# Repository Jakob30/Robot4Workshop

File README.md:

# Roboterarm – Aufbau und Inbetriebnahme

Dieses Projekt beschreibt den Aufbau und die Inbetriebnahme eines Roboterarms, der mithilfe von 3D-gedruckten Teilen, einer selbstgefertigten Platine und einem STM32F4-Mikrocontroller gesteuert wird.  

---

## 📦 Vorbereitung

1. **3D-Druckteile**  
   - Alle benötigten Teile laut STL-Dateien ausdrucken. Detaillierte Anweisungen befinden sich in dieser [README im Roboterarm Ordner](./Roboterarm/README.md).
   - Qualität und Stabilität der Teile prüfen.  

2. **Bestellung von Bauteilen**  
   - Alle mechanischen und elektronischen Komponenten von der Bestellliste besorgen.  

---

## 🔧 Zusammenbau

Wenn alle 3D-Druckteile und Bauteile vorhanden sind, den Arm gemäß der [**Montageanleitung**](./Roboterarm/Montagehinweise.pdf) zusammenbauen.   

---

## 🖥️ Platine (PCB)

1. **Fertigung**  
   - Platinendaten herunterladen und bei einem Hersteller fertigen lassen. Hinweise zur Platinenfertigung findet man im [Elektronik Ordner](./Elektronik/README.md).

2. **Bestückung**  
   - Bauteile wie Headerpins und Widerstände auf die Platine löten (siehe [README im Elektronik Ordner](./Elektronik/README.md)).  
   - Anschließend können Treiber, Nucleoboard und OLED aufgesteckt werden.

3. **Stromversorgung**  
   - Ein zusätzliches Kabel löten, das den Akku mit der Sicherung, dem Schalter und anschließend mit dem DC/DC-Wandler verbindet.  

---

## ⚙️ STM32F4 – Software

1. **Setup**  
   - [STM32CubeIDE](https://www.st.com/en/development-tools/stm32cubeide.html) installieren.  
   - Projektdateien aus [STM32F4 Ordner](./STM32F4/) importieren.
  
2. **Stromversorgung**  
   - Platine mit Akku oder Netzgerät mit Versorgungsspannung von ca. 15V verbinden.  
   - Schalter umlegen. 
  
3. **Anpassung** 
   - Bewegungen werden im `main.c` programmiert und alle aufzurufenden Funktionen sind in [README](./STM32F4/README.md) beschrieben.  
   - Code per USB auf den Mikrocontroller hochladen.  

---

## 🔍 Kalibrierung mit StallGuard

Vor der ersten Inbetriebnahme ist eine Kalibrierung der StallGuard-Werte notwendig.  
Empfohlen wird die Nutzung von **STM32CubeMonitor**, um Variablen in Echtzeit auszulesen.  

Wichtige Parameter:  
- `STALL_BUFFER_M_X`  
- `LOW_COUNTER_THRESHOLD_M_X`  
- `STALL_MAX_M_X`  

---

## ▶️ Start

1. Vor dem Start den **schwarzen Reset-Knopf** am Nucleo-Board drücken.  
2. Mit dem **blauen Userbutton** das Programm starten.  

---

## 🎥 Beispielvideo

Einen Eindruck, wie der fertige Roboterarm aussehen kann, gibt es hier:  
[➡️ Video ansehen](https://www.dropbox.com/scl/fi/g09jmz12r2tmc5cvw9wto/Robot4Workshop_v4.mp4?rlkey=lwdefdrdfxj2pr9vu0g0xlj73&st=269ooo00&dl=0)

---

## ✅ Hinweis

- Alle Arbeitsschritte sorgfältig durchführen.  
- Sicherheitsaspekte beim Umgang mit Stromversorgung und Lötarbeiten beachten.

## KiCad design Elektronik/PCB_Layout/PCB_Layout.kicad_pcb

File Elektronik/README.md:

# Elektronik – PCB_Layout (KiCad)

Diese README beschreibt **alles rund um die Leiterplatte**: warum KiCad, was im Ordner `PCB_Layout/` liegt, wie du die Platine **fertigen lässt**, **Bauteile bestellst**, **bestückst** und **in Betrieb nimmst**.

---

## Warum KiCad?

* **Open‑Source & kostenlos**: Reproduzierbar für alle – ideal für ein Open‑Hardware‑Projekt.
* **Versionierbar**: Textbasierte Projektdateien → gut in Git nutzbar.
* **Ökosystem**: iBOM, DRC/ERC‑Checks, Plugin‑Support.

> Getestet mit **KiCad 8.x**. Ältere Versionen funktionieren u. U. nicht.

---

## Ordnerstruktur

```
Elektronik/
└─ PCB_Layout/
   ├─ PCB_Layout.kicad_pro           # Projektdatei (KiCad 8)
   ├─ PCB_Layout.kicad_sch           # Top‑Schaltplan (inkl. Hierarchie)
   ├─ PCB_Layout.kicad_pcb           # Leiterplattenlayout
   ├─ power.kicad_sch                # Sheet: Versorgung/15 V → 5 V 
   ├─ nucleo_F446RE.kicad_sch        # Sheet: NUCLEO‑F446RE 
   ├─ motor_driver.kicad_sch         # Sheet: TMC2209‑Treiber & Motoranschlüsse
   ├─ display_und_LED.kicad_sch      # Sheet: OLED, LEDs
   ├─ AOM12864A0-1.54WW-ANO/         # **Custom Footprint/Symbol** (OLED 1.54")
   ├─ DM-OLED096-636/                # **Custom Footprint/Symbol** (OLED 0.96")
   ├─ NUCLEO-F446RE/                 # **Custom Footprint/Symbol** (Nucleo STM32)
   ├─ TMC2209_SILENTSTEPSTICK/       # **Custom Footprint/Symbol** (Treiber‑Modul)
   ├─ PCB_Layout----
```

**Hinweis zu den Unterordnern:** `AOM12864…`, `DM‑OLED096‑636`, `NUCLEO‑F446RE`, `TMC2209_SILENTSTEPSTICK` enthalten die **projektspezifischen Bibliotheken** (Symbole/Footprints), die **nicht in KiCads Standard‑Libs** vorhanden sind. Damit bleibt das Projekt **voll reproduzierbar**.

---

## Platinenfertigung – Schritt für Schritt

### 1) Gerber/Bohrdaten erzeugen (KiCad)

1. Projekt öffnen → PCB-Editor.
2. **Datei → Plot**

   * Format: **Gerber**
   * Lagen (typisch 2‑lagig): `F.Cu`, `B.Cu`, `F.SilkS`, `B.SilkS`, `F.Mask`, `B.Mask`, `Edge.Cuts` (ggf. `F.Paste/B.Paste` bei Reflow‑SMD)
   * Allgemeine Optionen → Abwählen **Footprintwerte plotten**
   * **Plotten** → anschl. **Bohrdateien generieren**.

3. **ZIP‑Archiv** aus allen Gerber + Drill → `fabrication/<projekt>_gerbers.zip`.

### 2) Hersteller auswählen & bestellen

Wir haben u. a. bei **Multi‑CB** (Multi Circuit Boards) gefertigt: [https://portal.multi-circuit-boards.eu/](https://portal.multi-circuit-boards.eu/)

**Vorgehen (Beispiel Multi‑CB):**

1. Portal öffnen → Online‑Kalkulator → **Optional: CAD-Datei automatisch auslesen** klicken → **Datei anhängen** und dann `fabrication/<projekt>_gerbers.zip` hochladen.
2. Stückzahl auswählen (z. B. 5–10 Stück) & Lieferzeit.
4. Bestellung abschließen.

> Andere Fertiger funktionieren ebenso, solange sie Standard‑Gerber akzeptieren.

---

## Stückliste (BOM) & Bauteilbestellung

### 1) BOM in KiCad erzeugen

* **Schaltplan‑Editor → Werkzeuge → Stückliste (BoM) erstellen** 
* **Exportieren** als CSV → `outputs/bom.csv`.

### 2) Teile kaufen

* Öffne `bom.csv` → bestelle nach **MPN** (Manufacturer Part Number) bei Distributor deiner Wahl (z. B. Conrad, Mouser, etc.).
* Die restlichen Module (z. B. **TMC2209 Treiber**, **NUCLEO‑F446RE**, **OLED 0.96"**) findest du in [dieser Bestellliste](../Bestellliste.xlsx)

> Tipp: SMD Widerstände/Kondensatoren sind i. d. R. 1206 Hand‑Solder‑freundlich.

---

## Bestückung & Montage

### Reihenfolge (empfohlen)

1. **SMD zuerst**, klein → groß (falls SMD vorhanden). Reflow oder Handlötung.
2. **THT** (Stiftleisten, Buchsenleisten, Schraubklemmen).

>Hinweis: Unten auf dem PCB sieht man, dass die Treiber, MCU und OLED Display direkt auf dem PCB gelötet werden können. Allerdings empfehlen wir, die Buchsenleisten an diesen Stellen zu löten und dann Treiber, MCU, Display darauf zu stecken. Damit lassen sich diese Bauteile problemlos ein-/ausstecken, ohne entlöten zu müssen. 

3. **Module** stecken:

   * **TMC2209**‑Module in korrekter **Orientierung** (Silkscreen‑Pfeile/Pin‑1). **Falsches Stecken zerstört den Treiber!**
   * **NUCLEO‑F446RE** Board/Socket einsetzen.
   * **OLED/LEDs** nach Polung.

> **Nie** Module stecken/ziehen, solange die Platine unter Spannung steht.

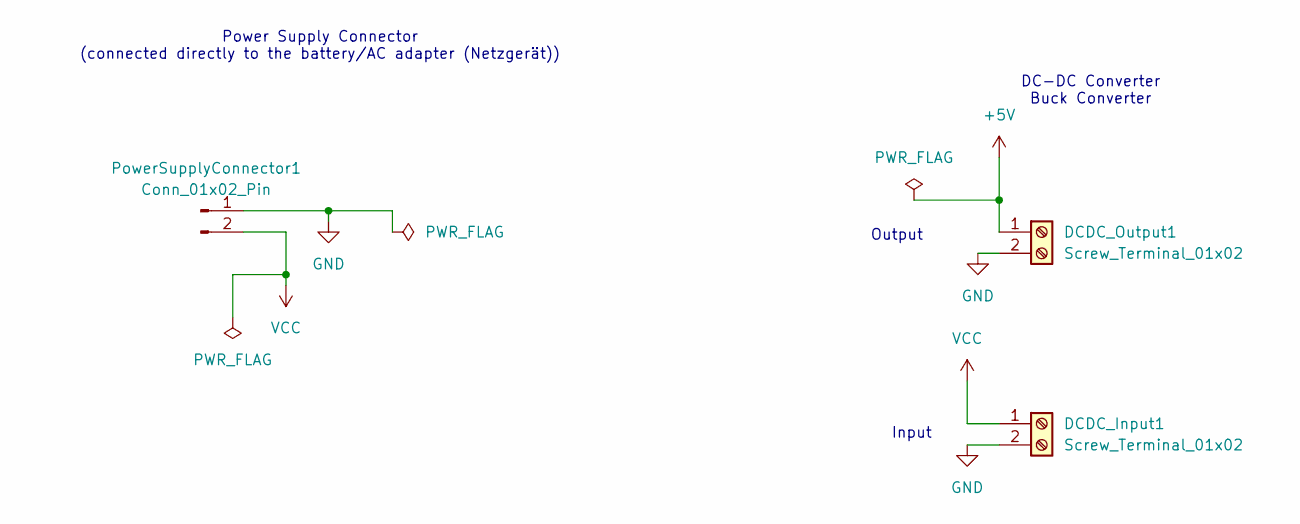
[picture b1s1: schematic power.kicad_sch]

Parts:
DCDC_Input1: Screw_Terminal_01x02; TerminalBlock_Phoenix_PT-1,5-2-5.0-H_1x02_P5.00mm_Horizontal
DCDC_Output1: Screw_Terminal_01x02; DC_DC_Converter_with_Screw_Terminal
PowerSupplyConnector1: Conn_01x02_Pin; AMASS_XT60-M_1x02_P7.20mm_Vertical

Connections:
+5V: DCDC_Output1.1; also elsewhere on the board
GND: DCDC_Input1.2, DCDC_Output1.2, PowerSupplyConnector1.1; also elsewhere on the board
VCC: DCDC_Input1.1, PowerSupplyConnector1.2; also elsewhere on the board

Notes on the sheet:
Input
Power Supply Connector (connected directly to the battery/AC adapter (Netzgerät))
Output
DC-DC Converter Buck Converter

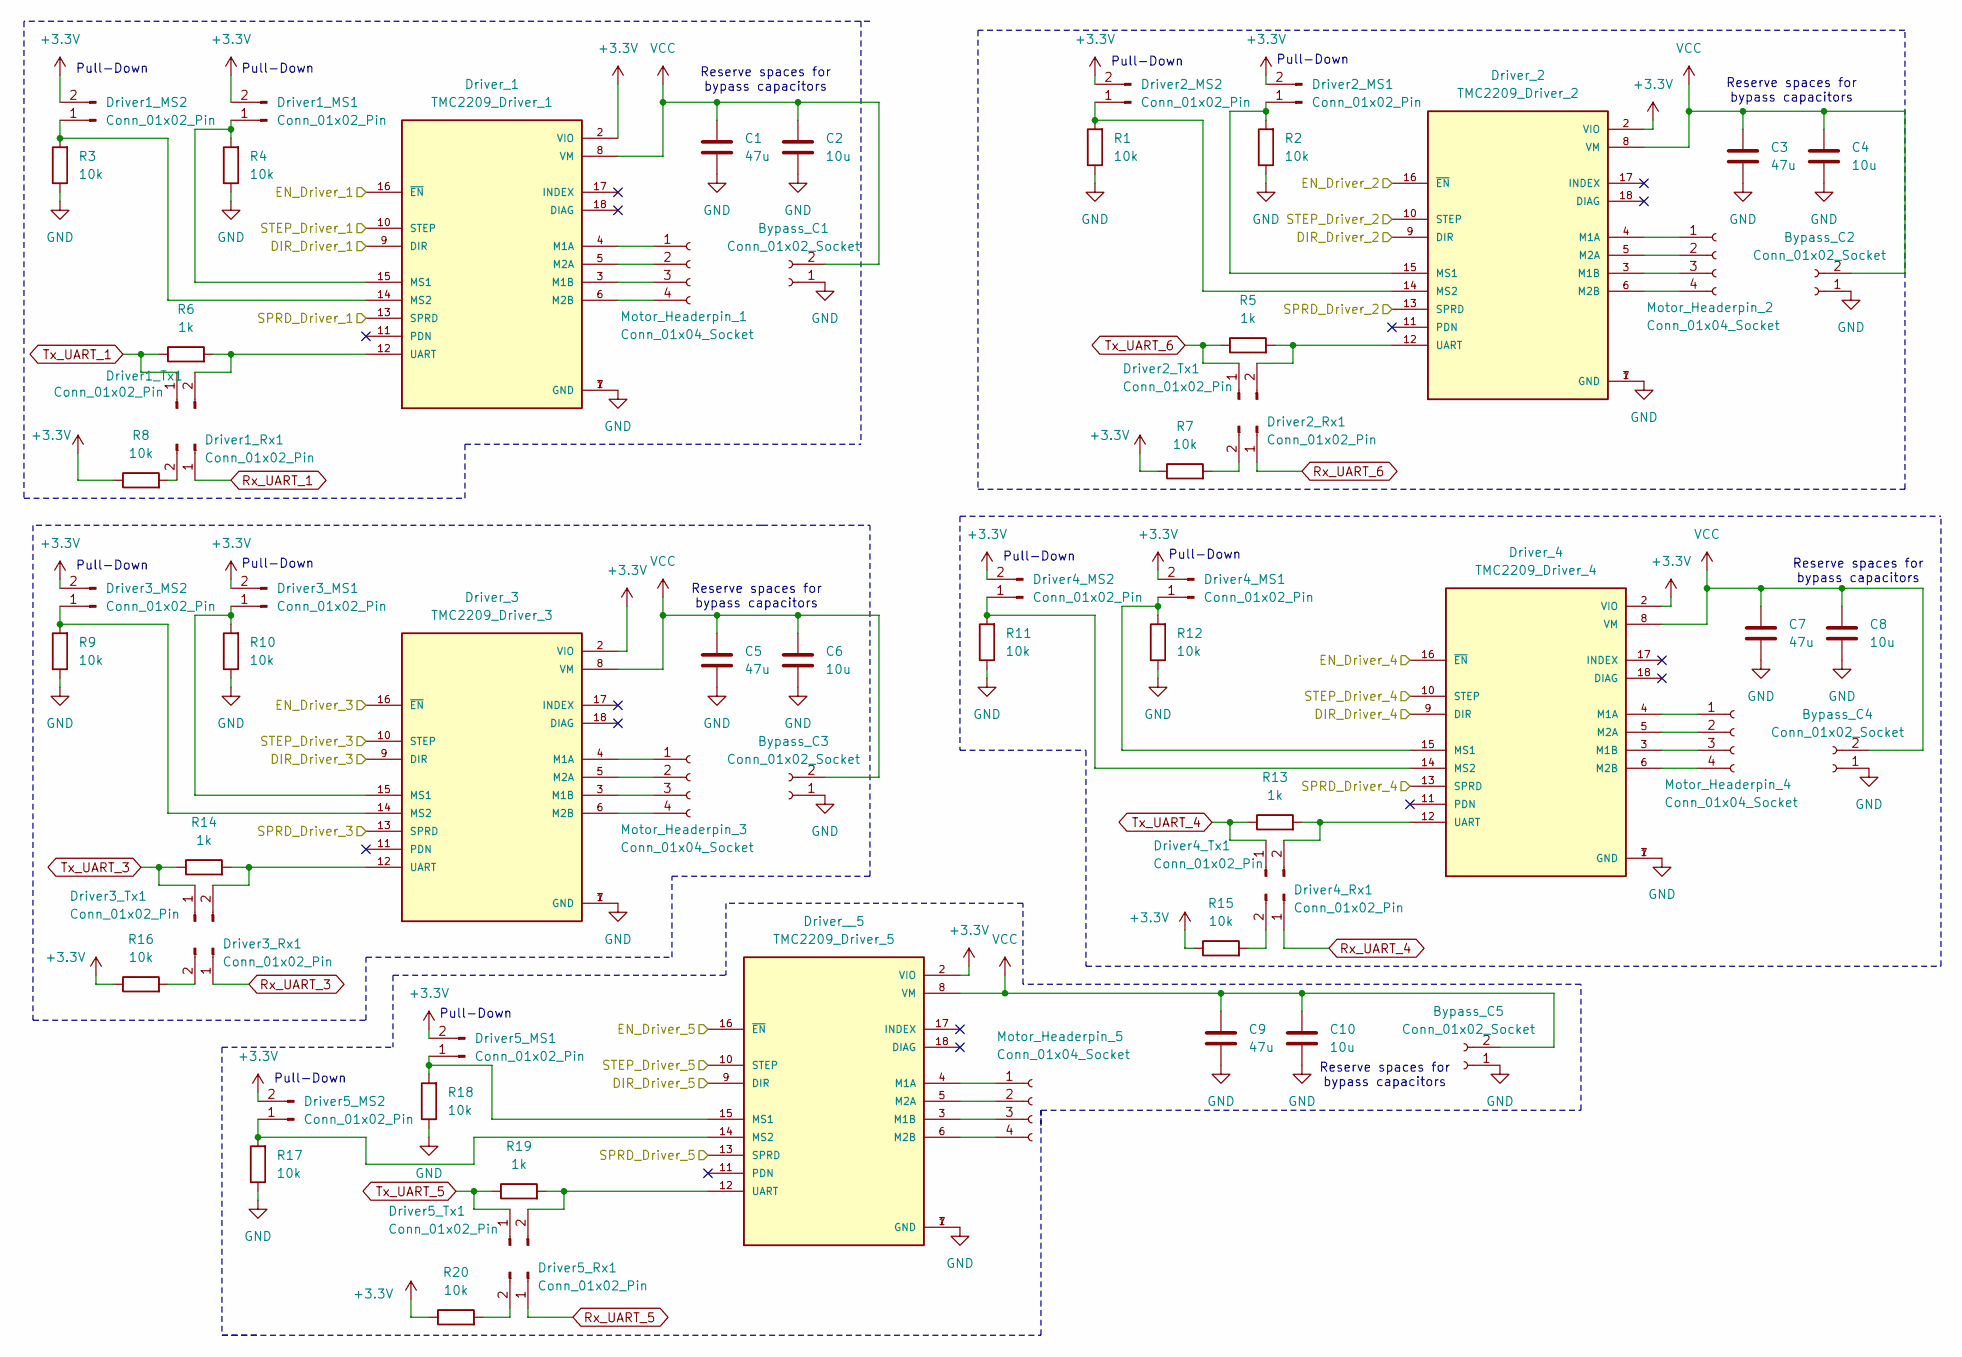
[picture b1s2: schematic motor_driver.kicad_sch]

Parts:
Bypass_C1, Bypass_C2, Bypass_C3, Bypass_C4, Bypass_C5: Conn_01x02_Socket; PinSocket_1x02_P2.54mm_Vertical_SMD_Pin1Left
C1, C3, C5, C7, C9: 47u; C_1206_3216Metric_Pad1.33x1.80mm_HandSolder
C2, C4, C6, C8, C10: 10u; C_1206_3216Metric_Pad1.33x1.80mm_HandSolder
Driver1_MS1, Driver1_MS2, Driver1_Rx1, Driver1_Tx1, Driver2_MS1, Driver2_MS2, Driver2_Rx1, Driver2_Tx1, Driver3_MS1, Driver3_MS2, Driver3_Rx1, Driver3_Tx1, Driver4_MS1, Driver4_MS2, Driver4_Rx1, Driver4_Tx1, Driver5_MS1, Driver5_MS2, Driver5_Rx1, Driver5_Tx1: Conn_01x02_Pin; PinHeader_1x02_P2.54mm_Vertical_SMD_Pin1Left
Driver_1: TMC2209_Driver_1; MODULE_TMC2209_SILENTSTEPSTICK; PARTREV 1.20
Driver_2: TMC2209_Driver_2; MODULE_TMC2209_SILENTSTEPSTICK; PARTREV 1.20
Driver_3: TMC2209_Driver_3; MODULE_TMC2209_SILENTSTEPSTICK; PARTREV 1.20
Driver_4: TMC2209_Driver_4; MODULE_TMC2209_SILENTSTEPSTICK; PARTREV 1.20
Driver__5: TMC2209_Driver_5; MODULE_TMC2209_SILENTSTEPSTICK; PARTREV 1.20
Motor_Headerpin_1, Motor_Headerpin_2, Motor_Headerpin_3, Motor_Headerpin_4, Motor_Headerpin_5: Conn_01x04_Socket; PinSocket_1x04_P2.54mm_Vertical
R1, R2, R3, R4, R7, R8, R9, R10, R11, R12, R15, R16, R17, R18, R20: 10k; R_1206_3216Metric_Pad1.30x1.75mm_HandSolder
R5, R6, R13, R14, R19: 1k; R_1206_3216Metric_Pad1.30x1.75mm_HandSolder

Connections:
+3.3V: Driver1_MS1.2, Driver1_MS2.2, Driver2_MS1.2, Driver2_MS2.2, Driver3_MS1.2, Driver3_MS2.2, Driver4_MS1.2, Driver4_MS2.2, Driver5_MS1.2, Driver5_MS2.2, Driver_1.2 (VIO), Driver_2.2 (VIO), Driver_3.2 (VIO), Driver_4.2 (VIO), Driver__5.2 (VIO), R7.1, R8.1, R15.1, R16.1, R20.1; also elsewhere on the board
/motor_driver/DIR_Driver_1: Driver_1.9 (DIR); also elsewhere on the board
/motor_driver/DIR_Driver_2: Driver_2.9 (DIR); also elsewhere on the board
/motor_driver/DIR_Driver_3: Driver_3.9 (DIR); also elsewhere on the board
/motor_driver/DIR_Driver_4: Driver_4.9 (DIR); also elsewhere on the board
/motor_driver/DIR_Driver_5: Driver__5.9 (DIR); also elsewhere on the board
/motor_driver/EN_Driver_1: Driver_1.16 (~EN); also elsewhere on the board
/motor_driver/EN_Driver_2: Driver_2.16 (~EN); also elsewhere on the board
/motor_driver/EN_Driver_3: Driver_3.16 (~EN); also elsewhere on the board
/motor_driver/EN_Driver_4: Driver_4.16 (~EN); also elsewhere on the board
/motor_driver/EN_Driver_5: Driver__5.16 (~EN); also elsewhere on the board
/motor_driver/SPRD_Driver_1: Driver_1.13 (SPRD); also elsewhere on the board
/motor_driver/SPRD_Driver_2: Driver_2.13 (SPRD); also elsewhere on the board
/motor_driver/SPRD_Driver_3: Driver_3.13 (SPRD); also elsewhere on the board
/motor_driver/SPRD_Driver_4: Driver_4.13 (SPRD); also elsewhere on the board
/motor_driver/SPRD_Driver_5: Driver__5.13 (SPRD); also elsewhere on the board
/motor_driver/STEP_Driver_1: Driver_1.10 (STEP); also elsewhere on the board
/motor_driver/STEP_Driver_2: Driver_2.10 (STEP); also elsewhere on the board
/motor_driver/STEP_Driver_3: Driver_3.10 (STEP); also elsewhere on the board
/motor_driver/STEP_Driver_4: Driver_4.10 (STEP); also elsewhere on the board
/motor_driver/STEP_Driver_5: Driver__5.10 (STEP); also elsewhere on the board
GND: Bypass_C1.1, Bypass_C2.1, Bypass_C3.1, Bypass_C4.1, Bypass_C5.1, C1.2, C2.2, C3.2, C4.2, C5.2, C6.2, C7.2, C8.2, C9.2, C10.2, Driver_1.1 (GND), Driver_1.7 (GND), Driver_2.1 (GND), Driver_2.7 (GND), Driver_3.1 (GND), Driver_3.7 (GND), Driver_4.1 (GND), Driver_4.7 (GND), Driver__5.1 (GND), Driver__5.7 (GND), R1.1, R2.1, R3.1, R4.1, R9.1, R10.1, R11.1, R12.1, R17.1, R18.1; also elsewhere on the board
unnamed: Driver1_MS1.1, Driver_1.15 (MS1), R4.2
unnamed: Driver1_MS2.1, Driver_1.14 (MS2), R3.2
unnamed: Driver1_Rx1.2, R8.2
unnamed: Driver1_Tx1.2, Driver_1.12 (UART), R6.2
unnamed: Driver2_MS1.1, Driver_2.15 (MS1), R2.2
unnamed: Driver2_MS2.1, Driver_2.14 (MS2), R1.2
unnamed: Driver2_Rx1.2, R7.2
unnamed: Driver2_Tx1.2, Driver_2.12 (UART), R5.2
unnamed: Driver3_MS1.1, Driver_3.15 (MS1), R10.2
unnamed: Driver3_MS2.1, Driver_3.14 (MS2), R9.2
unnamed: Driver3_Rx1.2, R16.2
unnamed: Driver3_Tx1.2, Driver_3.12 (UART), R14.2
unnamed: Driver4_MS1.1, Driver_4.15 (MS1), R12.2
unnamed: Driver4_MS2.1, Driver_4.14 (MS2), R11.2
unnamed: Driver4_Rx1.2, R15.2
unnamed: Driver4_Tx1.2, Driver_4.12 (UART), R13.2
unnamed: Driver5_MS1.1, Driver__5.15 (MS1), R18.2
unnamed: Driver5_MS2.1, Driver__5.14 (MS2), R17.2
unnamed: Driver5_Rx1.2, R20.2
unnamed: Driver5_Tx1.2, Driver__5.12 (UART), R19.2
unnamed: Driver_1.4 (M1A), Motor_Headerpin_1.1
unnamed: Driver_1.3 (M1B), Motor_Headerpin_1.3
unnamed: Driver_1.5 (M2A), Motor_Headerpin_1.2
unnamed: Driver_1.6 (M2B), Motor_Headerpin_1.4
unnamed: Driver_2.4 (M1A), Motor_Headerpin_2.1
unnamed: Driver_2.3 (M1B), Motor_Headerpin_2.3
unnamed: Driver_2.5 (M2A), Motor_Headerpin_2.2
unnamed: Driver_2.6 (M2B), Motor_Headerpin_2.4
unnamed: Driver_3.4 (M1A), Motor_Headerpin_3.1
unnamed: Driver_3.3 (M1B), Motor_Headerpin_3.3
unnamed: Driver_3.5 (M2A), Motor_Headerpin_3.2
unnamed: Driver_3.6 (M2B), Motor_Headerpin_3.4
unnamed: Driver_4.4 (M1A), Motor_Headerpin_4.1
unnamed: Driver_4.3 (M1B), Motor_Headerpin_4.3
unnamed: Driver_4.5 (M2A), Motor_Headerpin_4.2
unnamed: Driver_4.6 (M2B), Motor_Headerpin_4.4
unnamed: Driver__5.4 (M1A), Motor_Headerpin_5.1
unnamed: Driver__5.3 (M1B), Motor_Headerpin_5.3
unnamed: Driver__5.5 (M2A), Motor_Headerpin_5.2
unnamed: Driver__5.6 (M2B), Motor_Headerpin_5.4
Rx_UART_1: Driver1_Rx1.1; also elsewhere on the board
Rx_UART_3: Driver3_Rx1.1; also elsewhere on the board
Rx_UART_4: Driver4_Rx1.1; also elsewhere on the board
Rx_UART_5: Driver5_Rx1.1; also elsewhere on the board
Rx_UART_6: Driver2_Rx1.1; also elsewhere on the board
Tx_UART_1: Driver1_Tx1.1, R6.1; also elsewhere on the board
Tx_UART_3: Driver3_Tx1.1, R14.1; also elsewhere on the board
Tx_UART_4: Driver4_Tx1.1, R13.1; also elsewhere on the board
Tx_UART_5: Driver5_Tx1.1, R19.1; also elsewhere on the board
Tx_UART_6: Driver2_Tx1.1, R5.1; also elsewhere on the board
VCC: Bypass_C1.2, Bypass_C2.2, Bypass_C3.2, Bypass_C4.2, Bypass_C5.2, C1.1, C2.1, C3.1, C4.1, C5.1, C6.1, C7.1, C8.1, C9.1, C10.1, Driver_1.8 (VM), Driver_2.8 (VM), Driver_3.8 (VM), Driver_4.8 (VM), Driver__5.8 (VM); also elsewhere on the board

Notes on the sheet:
Reserve spaces for bypass capacitors
Pull-Down
Reserve spaces for bypass capacitors

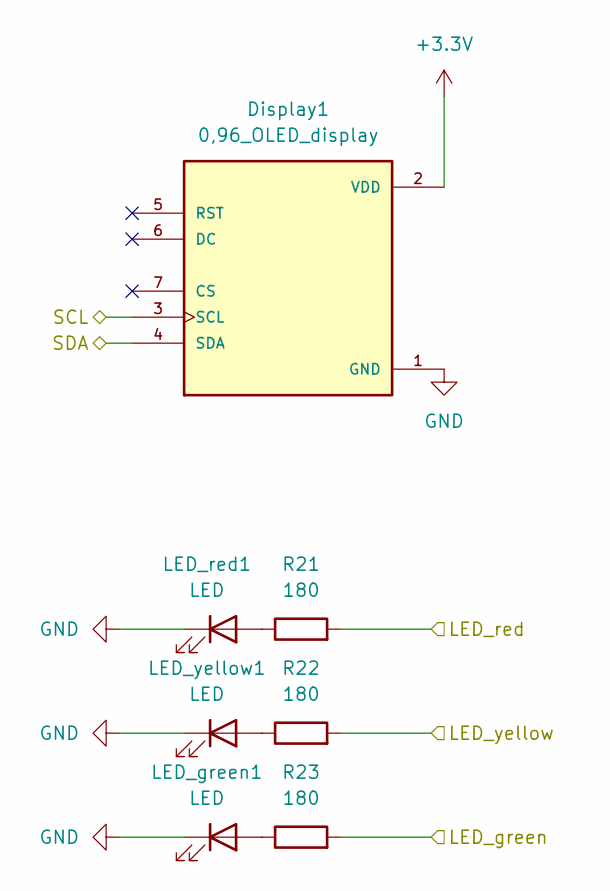
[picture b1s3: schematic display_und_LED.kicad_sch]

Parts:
Display1: 0,96_OLED_display; 0,96_OLED_Display; PARTREV O
LED_green1: LED; LED_D5.0mm
LED_red1: LED; LED_D5.0mm
LED_yellow1: LED; LED_D5.0mm
R21, R22, R23: 180; R_1206_3216Metric_Pad1.30x1.75mm_HandSolder

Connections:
+3.3V: Display1.2 (VDD); also elsewhere on the board
/display_und_LED/LED_green: R23.2; also elsewhere on the board
/display_und_LED/LED_red: R21.2; also elsewhere on the board
/display_und_LED/LED_yellow: R22.2; also elsewhere on the board
/display_und_LED/SCL: Display1.3 (SCL); also elsewhere on the board
/display_und_LED/SDA: Display1.4 (SDA); also elsewhere on the board
GND: Display1.1 (GND), LED_green1.1 (K), LED_red1.1 (K), LED_yellow1.1 (K); also elsewhere on the board
unnamed: LED_green1.2 (A), R23.1
unnamed: LED_red1.2 (A), R21.1
unnamed: LED_yellow1.2 (A), R22.1

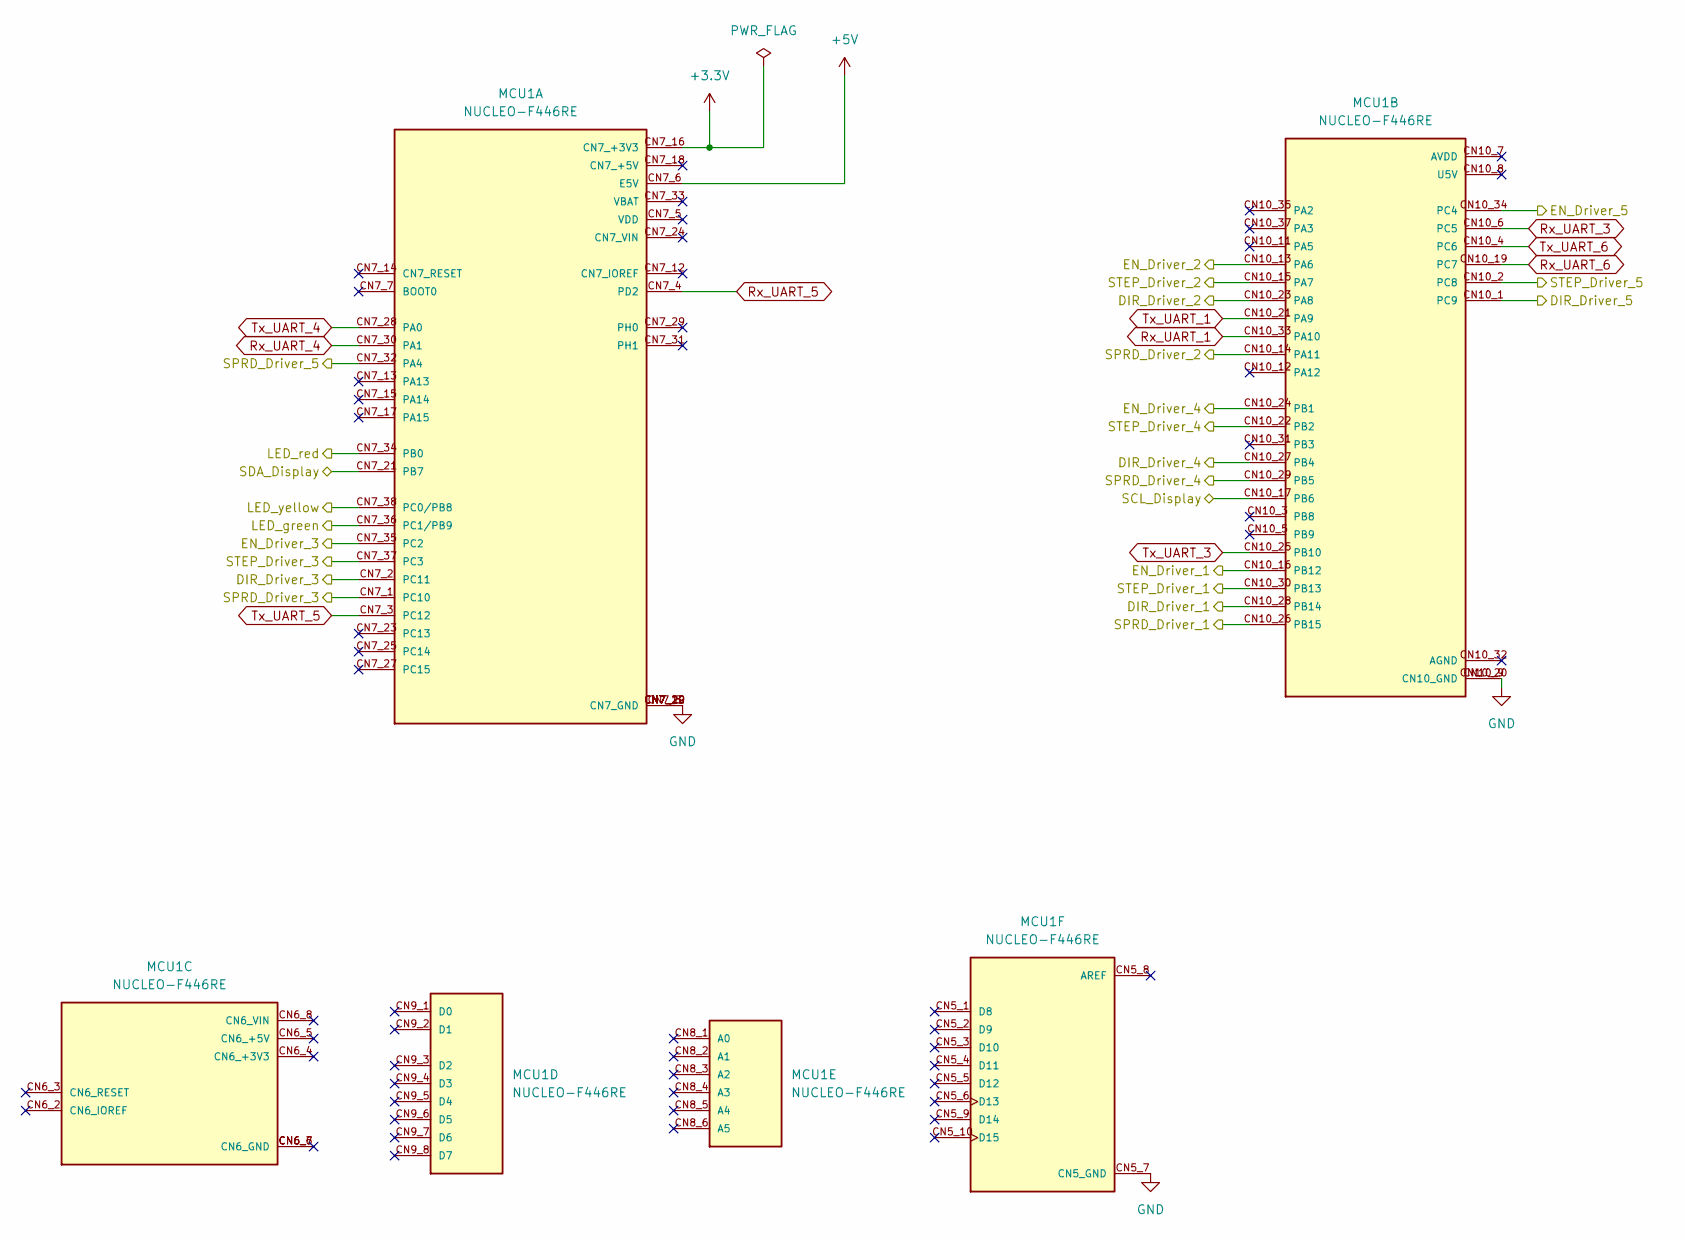
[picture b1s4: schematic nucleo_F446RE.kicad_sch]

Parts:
MCU1: NUCLEO-F446RE; MODULE_NUCLEO-F446RE; PARTREV 13

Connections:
+3.3V: MCU1.CN7_16 (CN7_+3V3); also elsewhere on the board
+5V: MCU1.CN7_6 (E5V); also elsewhere on the board
/display_und_LED/LED_green: MCU1.CN7_36 (PC1/PB9); also elsewhere on the board
/display_und_LED/LED_red: MCU1.CN7_34 (PB0); also elsewhere on the board
/display_und_LED/LED_yellow: MCU1.CN7_38 (PC0/PB8); also elsewhere on the board
/display_und_LED/SCL: MCU1.CN10_17 (PB6); also elsewhere on the board
/display_und_LED/SDA: MCU1.CN7_21 (PB7); also elsewhere on the board
/motor_driver/DIR_Driver_1: MCU1.CN10_28 (PB14); also elsewhere on the board
/motor_driver/DIR_Driver_2: MCU1.CN10_23 (PA8); also elsewhere on the board
/motor_driver/DIR_Driver_3: MCU1.CN7_2 (PC11); also elsewhere on the board
/motor_driver/DIR_Driver_4: MCU1.CN10_27 (PB4); also elsewhere on the board
/motor_driver/DIR_Driver_5: MCU1.CN10_1 (PC9); also elsewhere on the board
/motor_driver/EN_Driver_1: MCU1.CN10_16 (PB12); also elsewhere on the board
/motor_driver/EN_Driver_2: MCU1.CN10_13 (PA6); also elsewhere on the board
/motor_driver/EN_Driver_3: MCU1.CN7_35 (PC2); also elsewhere on the board
/motor_driver/EN_Driver_4: MCU1.CN10_24 (PB1); also elsewhere on the board
/motor_driver/EN_Driver_5: MCU1.CN10_34 (PC4); also elsewhere on the board
/motor_driver/SPRD_Driver_1: MCU1.CN10_26 (PB15); also elsewhere on the board
/motor_driver/SPRD_Driver_2: MCU1.CN10_14 (PA11); also elsewhere on the board
/motor_driver/SPRD_Driver_3: MCU1.CN7_1 (PC10); also elsewhere on the board
/motor_driver/SPRD_Driver_4: MCU1.CN10_29 (PB5); also elsewhere on the board
/motor_driver/SPRD_Driver_5: MCU1.CN7_32 (PA4); also elsewhere on the board
/motor_driver/STEP_Driver_1: MCU1.CN10_30 (PB13); also elsewhere on the board
/motor_driver/STEP_Driver_2: MCU1.CN10_15 (PA7); also elsewhere on the board
/motor_driver/STEP_Driver_3: MCU1.CN7_37 (PC3); also elsewhere on the board
/motor_driver/STEP_Driver_4: MCU1.CN10_22 (PB2); also elsewhere on the board
/motor_driver/STEP_Driver_5: MCU1.CN10_2 (PC8); also elsewhere on the board
GND: MCU1.CN5_7 (CN5_GND), MCU1.CN7_8 (CN7_GND), MCU1.CN7_19 (CN7_GND), MCU1.CN7_20 (CN7_GND), MCU1.CN7_22 (CN7_GND), MCU1.CN10_9 (CN10_GND), MCU1.CN10_20 (CN10_GND); also elsewhere on the board
Rx_UART_1: MCU1.CN10_33 (PA10); also elsewhere on the board
Rx_UART_3: MCU1.CN10_6 (PC5); also elsewhere on the board
Rx_UART_4: MCU1.CN7_30 (PA1); also elsewhere on the board
Rx_UART_5: MCU1.CN7_4 (PD2); also elsewhere on the board
Rx_UART_6: MCU1.CN10_19 (PC7); also elsewhere on the board
Tx_UART_1: MCU1.CN10_21 (PA9); also elsewhere on the board
Tx_UART_3: MCU1.CN10_25 (PB10); also elsewhere on the board
Tx_UART_4: MCU1.CN7_28 (PA0); also elsewhere on the board
Tx_UART_5: MCU1.CN7_3 (PC12); also elsewhere on the board
Tx_UART_6: MCU1.CN10_4 (PC6); also elsewhere on the board

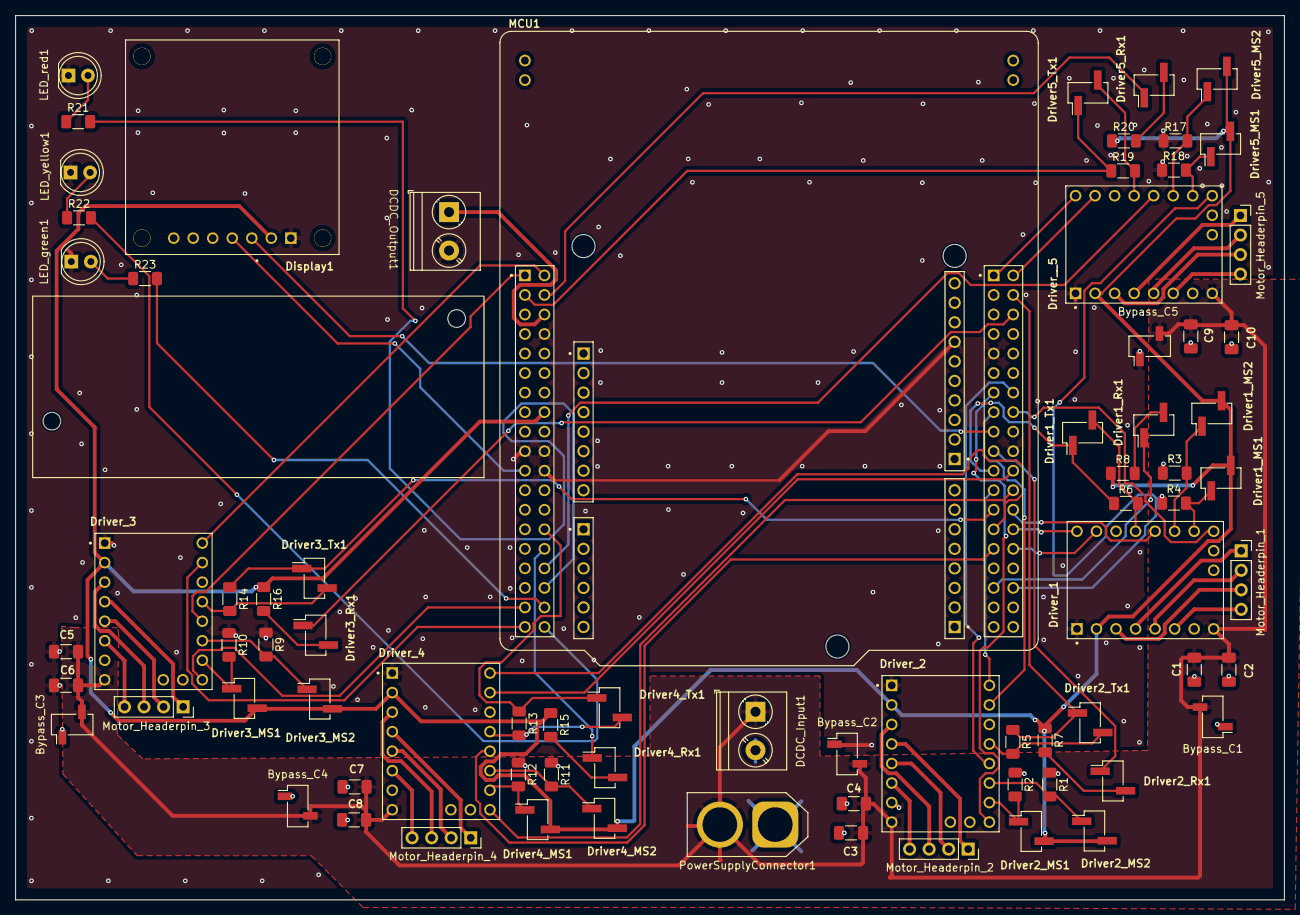
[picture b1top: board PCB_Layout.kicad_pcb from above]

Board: 2 copper layers, 165.0 x 115.0 mm, 76 parts (0 on the bottom side), 82 nets.

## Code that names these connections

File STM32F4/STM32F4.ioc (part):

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Mcu.Name=STM32F446R(C-E)Tx
Mcu.Package=LQFP64
Mcu.UserName=STM32F446RETx
PA0-WKUP.Mode=Asynchronous
PA0-WKUP.Signal=UART4_TX
PA1.Mode=Asynchronous
PA1.Signal=UART4_RX
PA10.Mode=Asynchronous
PA10.Signal=USART1_RX
PA11.Signal=GPIO_Input
PA13.GPIOParameters=GPIO_Label
PA13.GPIO_Label=TMS
PA13.Mode=Serial_Wire
PA13.Signal=SYS_JTMS-SWDIO
PA14.GPIOParameters=GPIO_Label
PA14.GPIO_Label=TCK
PA14.Mode=Serial_Wire
PA14.Signal=SYS_JTCK-SWCLK
PA2.GPIOParameters=GPIO_PuPd,GPIO_Label,GPIO_ModeDefaultOD
PA2.GPIO_Label=USART_TX
PA2.GPIO_ModeDefaultOD=GPIO_MODE_AF_OD
PA2.GPIO_PuPd=GPIO_NOPULL
PA2.Mode=Asynchronous
PA2.Signal=USART2_TX
PA3.GPIOParameters=GPIO_Label
PA3.GPIO_Label=USART_RX
PA3.Mode=Asynchronous
PA3.Signal=USART2_RX
PA4.Signal=GPIO_Input
PA5.GPIOParameters=GPIO_Label
PA5.GPIO_Label=LD2 [Green Led]
PA5.Signal=GPIO_Output
PA6.GPIOParameters=GPIO_Label
PA6.GPIO_Label=MOT_EN_2
PA6.Signal=GPIO_Output
PA7.GPIOParameters=GPIO_Label
PA7.GPIO_Label=STEP_2
PA7.Signal=GPIO_Output
PA8.GPIOParameters=GPIO_Label
PA8.GPIO_Label=DIR_2
PA8.Signal=GPIO_Output
PA9.GPIOParameters=GPIO_PuPd
PA9.GPIO_PuPd=GPIO_NOPULL
PA9.Mode=Asynchronous
PA9.Signal=USART1_TX
PB0.GPIOParameters=GPIO_Label
PB0.GPIO_Label=LED_red
PB0.Signal=GPIO_Output
PB1.GPIOParameters=GPIO_Label
PB1.GPIO_Label=MOT_EN_4
PB1.Signal=GPIO_Output
PB10.Mode=Asynchronous
PB10.Signal=USART3_TX
PB12.GPIOParameters=GPIO_Label
PB12.GPIO_Label=MOT_EN_1
PB12.Signal=GPIO_Output
PB13.GPIOParameters=GPIO_Label
PB13.GPIO_Label=STEP_1
PB13.Signal=GPIO_Output
PB14.GPIOParameters=GPIO_Label
PB14.GPIO_Label=DIR_1
PB14.Signal=GPIO_Output
PB15.Signal=GPIO_Input
PB2.GPIOParameters=GPIO_Label
PB2.GPIO_Label=STEP_4
PB2.Signal=GPIO_Output
PB3.GPIOParameters=GPIO_Label
PB3.GPIO_Label=SWO
PB3.Signal=SYS_JTDO-SWO
PB4.GPIOParameters=GPIO_Label
PB4.GPIO_Label=DIR_4
PB4.Signal=GPIO_Output
PB5.Signal=GPIO_Input
PB6.Mode=I2C
PB6.Signal=I2C1_SCL
PB7.Mode=I2C
PB7.Signal=I2C1_SDA
PB9.GPIOParameters=GPIO_Label
PB9.GPIO_Label=DIAG_3
PB9.Signal=GPIO_Input
PC0.GPIOParameters=GPIO_Label
PC0.GPIO_Label=LED_yellow
PC0.Signal=GPIO_Output
PC1.GPIOParameters=GPIO_Label
PC1.GPIO_Label=LED_green
PC1.Signal=GPIO_Output
PC10.Signal=GPIO_Input
PC11.GPIOParameters=GPIO_Label
PC11.GPIO_Label=DIR_3
PC11.Signal=GPIO_Output
PC12.Mode=Asynchronous
PC12.Signal=UART5_TX
PC13.GPIOParameters=GPIO_Label,GPIO_ModeDefaultEXTI
PC13.GPIO_Label=B1 [Blue PushButton]
PC13.GPIO_ModeDefaultEXTI=GPIO_MODE_IT_RISING
PC13.Signal=GPXTI13
PC14-OSC32_IN.Mode=LSE-External-Oscillator
PC14-OSC32_IN.Signal=RCC_OSC32_IN
PC15-OSC32_OUT.Mode=LSE-External-Oscillator
PC15-OSC32_OUT.Signal=RCC_OSC32_OUT
PC2.GPIOParameters=GPIO_Label
PC2.GPIO_Label=MOT_EN_3
PC2.Signal=GPIO_Output
PC3.GPIOParameters=GPIO_Label
PC3.GPIO_Label=STEP_3
PC3.Signal=GPIO_Output
PC4.GPIOParameters=GPIO_Label
PC4.GPIO_Label=MOT_EN_5
PC4.Signal=GPIO_Output
PC5.Mode=Asynchronous
PC5.Signal=USART3_RX
PC6.Mode=Asynchronous
PC6.Signal=USART6_TX
PC7.Mode=Asynchronous
PC7.Signal=USART6_RX
PC8.GPIOParameters=GPIO_Label
PC8.GPIO_Label=STEP_5
PC8.Signal=GPIO_Output
PC9.GPIOParameters=GPIO_Label
PC9.GPIO_Label=DIR_5
PC9.Signal=GPIO_Output
PD2.Mode=Asynchronous
PD2.Signal=UART5_RX
PH0-OSC_IN.Mode=HSE-External-Oscillator
PH0-OSC_IN.Signal=RCC_OSC_IN
PH1-OSC_OUT.Mode=HSE-External-Oscillator
PH1-OSC_OUT.Signal=RCC_OSC_OUT
RCC.HSE_VALUE=8000000
RCC.SYSCLKFreq_VALUE=84000000
RCC.SYSCLKSource=RCC_SYSCLKSOURCE_PLLCLK
board=NUCLEO-F446RE
boardIOC=true

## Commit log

2025-08-14 two motors at the same time working
2025-08-19 5 Motors working. Currently working on StallGuard implementation.
2025-08-29 stallguard implemented and working reliable, now working on fine tuning
2025-08-29 Sensorless Homing with stallGuard now works
2025-09-02 point to point implemented not yet working lol
2025-09-08 Added comments to explain operating principle
2025-09-08 goHome() and grip() function work reliable
2025-09-11 added openGripper() and code refactoring
2025-09-12 remove update V_MAX, modify openGripper while Homing
2025-09-13 Added kinematics_solver and tested move_to_Coordinate() in main
2025-09-15 Added LEDs
2025-09-16 organization of files and updated kinematics
2025-09-23 Added Creo8 CAD assembly and parts
2025-09-23 added option to use 2 UARTs instead of 5
2025-09-23 Added README
2025-09-23 reorganized files
2025-09-25 added error-handling
2025-09-29 STL files and STEP Model added
2025-09-29 two UART Mode implemented and tested
2025-09-29 added a README
2025-09-30 added instructions and order list to build roboter
2025-09-30 updated order list
2025-09-30 Readme updated
2025-09-30 Added Elektronik
2025-09-30 added comments and refactoring
2025-09-30 Schrauben zu Greifr hinzu
2025-09-30 Added Screws, washers, nuts
2025-10-01 Added Assembly description
2025-10-01 modified main README
2025-10-01 added LEDs green and yellow, modified Stall_Buffer_5
